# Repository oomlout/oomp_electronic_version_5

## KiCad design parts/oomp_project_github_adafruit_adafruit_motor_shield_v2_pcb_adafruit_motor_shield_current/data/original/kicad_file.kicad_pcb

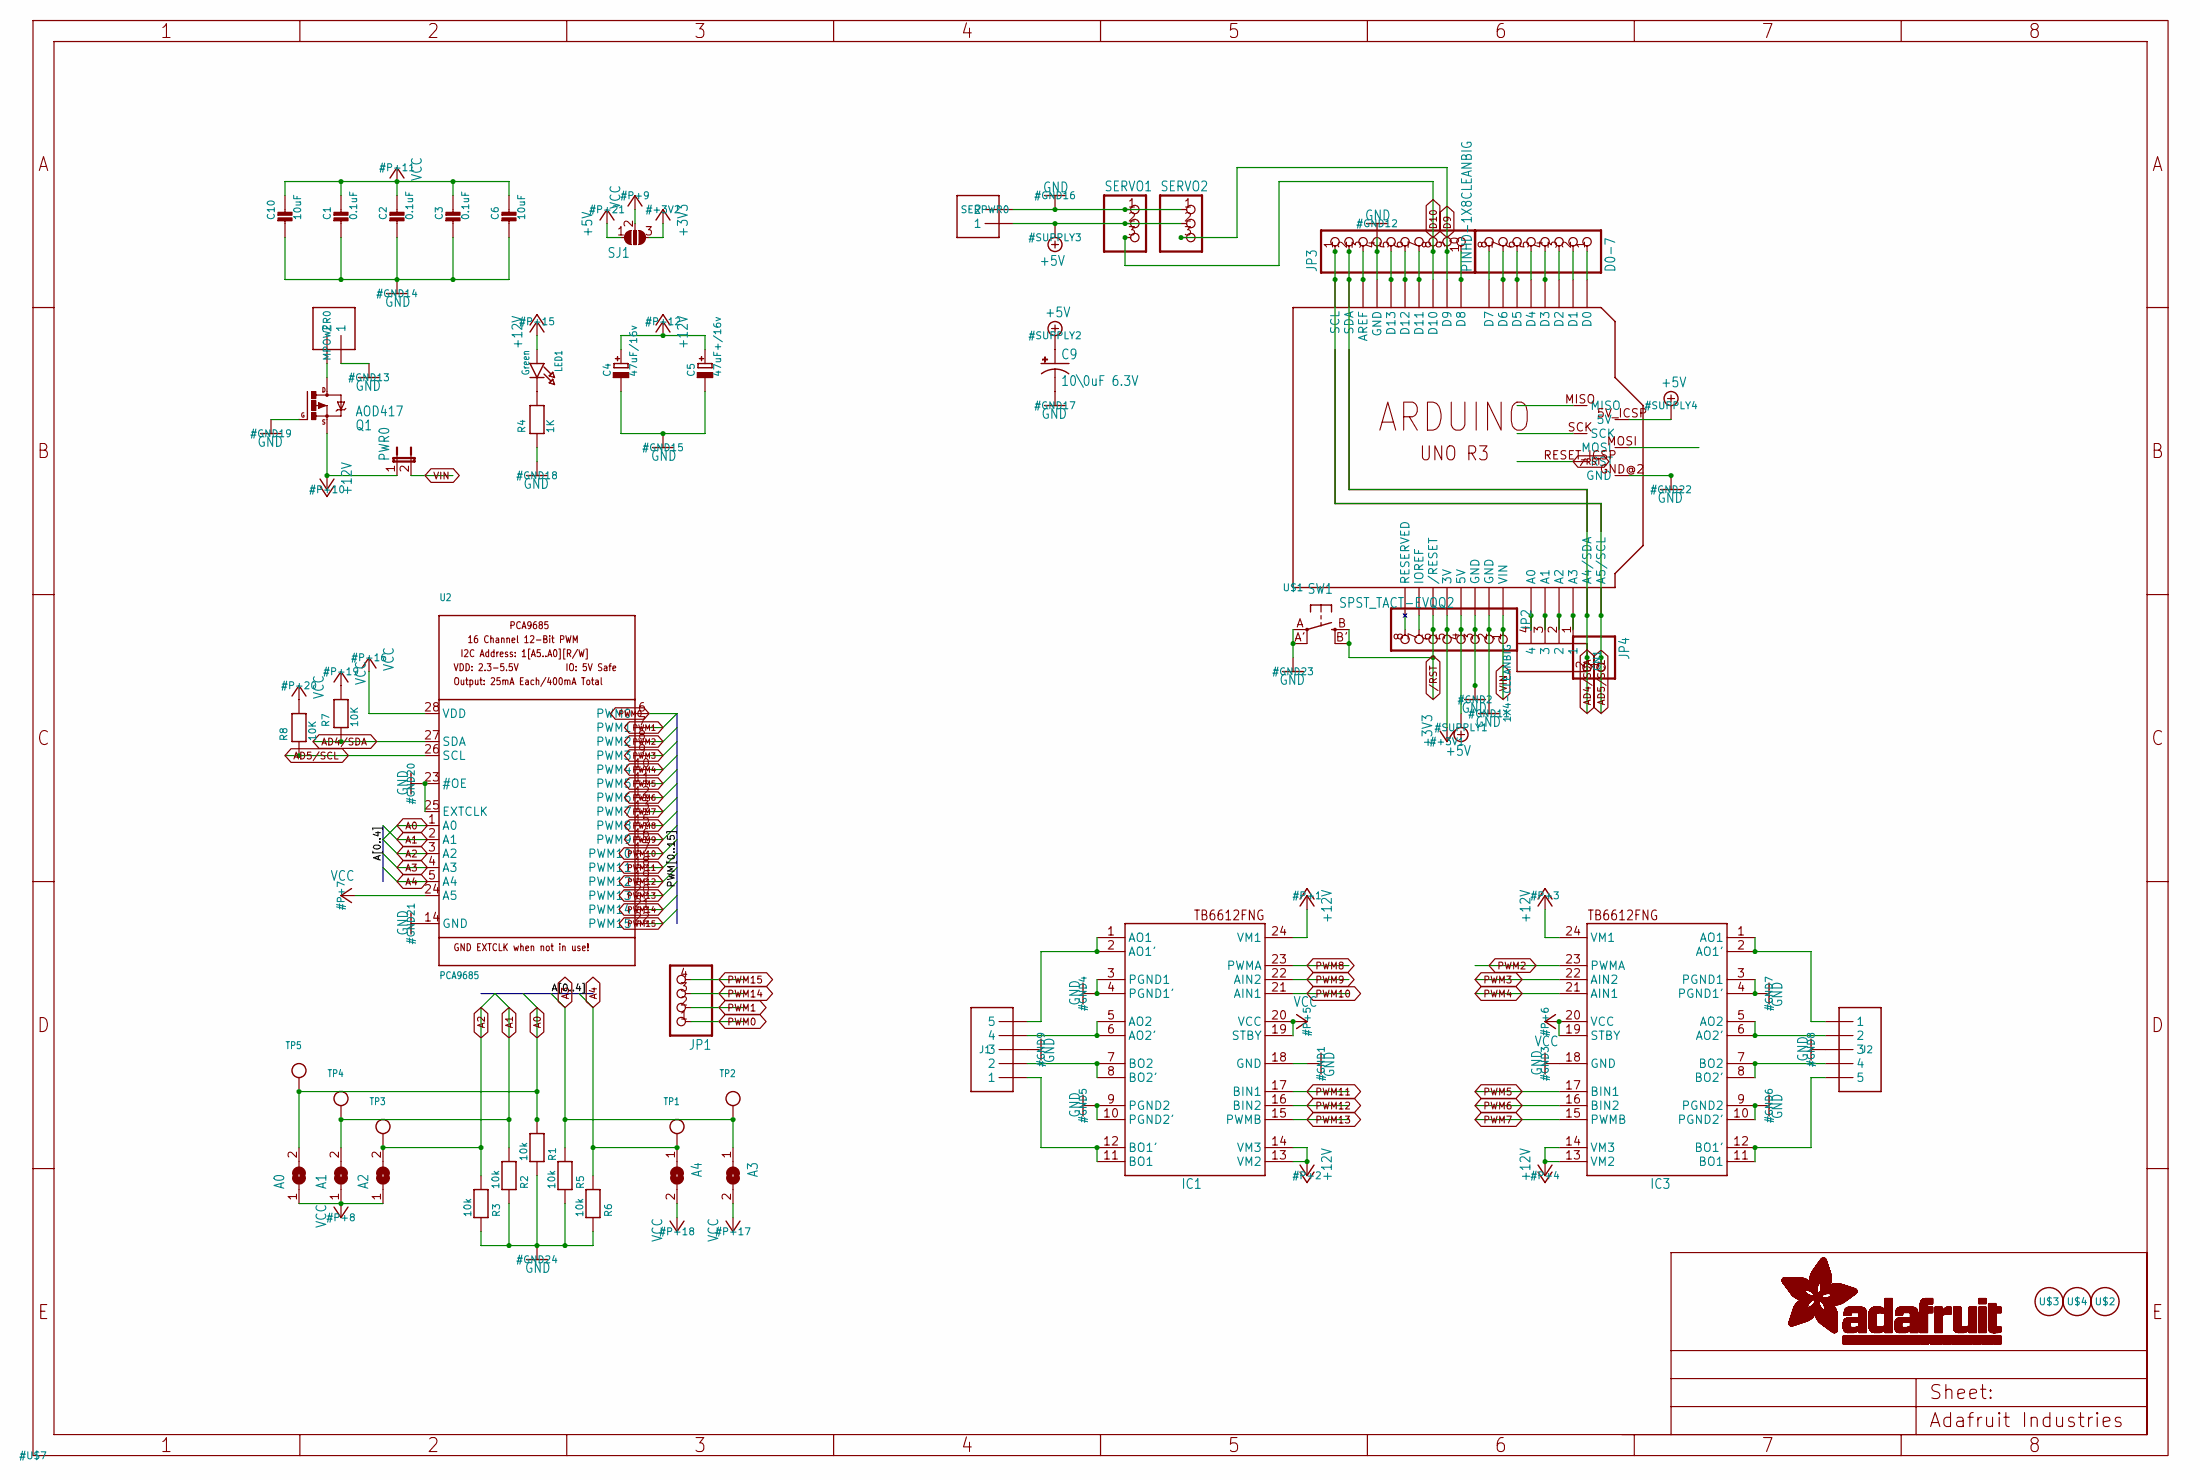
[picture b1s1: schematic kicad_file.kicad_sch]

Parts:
A0, A1, A2, A3, A4: SOLDERJUMPERREFLOW_NOPASTE; SOLDERJUMPER_REFLOW_NOPASTE
C1, C2, C3: 0.1uF; 0805-NO
C4: 47uF/16v; PANASONIC_C
C5: 47uF+/16v; PANASONIC_C
C6, C10: 10uF; 0805-NO
C9: 10\0uF 6.3V; PANASONIC_C
CN1: 1X4-CLEANBIG; 1X04-CLEANBIG
D0-7: PINHD-1X8CLEANBIG; 1X08-CLEANBIG
IC1, IC3: TB6612FNG; SSOP24
J1, J2: 1X5; 1X05-3.5MM
JP1: HEADER-1X476MIL; 1X04_ROUND_76
JP2: PINHD-1X8CLEANBIG; 1X08-CLEANBIG
JP3: HEADER-1X1070MIL; 1X10_ROUND70
JP4: HEADER-1X2ROUND; 1X02_ROUND
LED1: Green; CHIPLED_0805_NOOUTLINE
MPOWER0: 1X2-3.5MM
PWR0: JP1E; JP1
Q1: AOD417; D-PAK_TO252AA
R1, R2, R3, R5, R6: 10k; 0805-NO
R4: 1K; 0805-NO
R7, R8: 10K; 0805-NO
SERPWR0: 1X2-3.5MM
SERVO1, SERVO2: PINHD-1X3; 1X03
SJ1: SOLDERJUMPER_2WAY; SOLDERJUMPER_2WAY_OPEN_NOPASTE
SW1: SPST_TACT-EVQQ2; EVQ-Q2
TP1, TP2, TP3, TP4, TP5: TESTPOINTROUND2MM; TESTPOINT_ROUND_2MM
U2: PCA9685; TSSOP28
U$1: ARDUINO_R3_ICSP; ARDUINOR3_ICSP
U$2, U$3, U$4: FIDUCIAL; FIDUCIAL_1MM

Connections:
+3V3: JP2.5, SJ1.3, U$1.3V
+5V: C9.+, JP2.4, SERPWR0.1, SERVO1.2, SERVO2.2, SJ1.1, U$1.5V, U$1.5V_ICSP (5V)
+12V: C4.+, C5.+, IC1.13 (VM2), IC1.14 (VM3), IC1.24 (VM1), IC3.13 (VM2), IC3.14 (VM3), IC3.24 (VM1), LED1.A, PWR0.1, Q1.3 (S)
/RST: JP2.6, SW1.B (S), SW1.B' (S1), U$1.RESET (/RESET), U$1.RESET_ICSP (RST)
A0: A0.2, R1.2, TP5.P$1, U2.1 (A0)
A1: A1.2, R2.2, TP4.P$1, U2.2 (A1)
A2: A2.2, R3.2, TP3.P$1, U2.3 (A2)
A3: A3.1, R5.2, TP2.P$1, U2.4 (A3)
A4: A4.1, R6.2, TP1.P$1, U2.5 (A4)
AD0: CN1.4, U$1.A0
AD1: CN1.3, U$1.A1
AD2: CN1.2, U$1.A2
AD3: CN1.1, U$1.A3
AD4/SDA: JP3.2, JP4.2, R7.1, U2.27 (SDA), U$1.A4 (A4/SDA), U$1.SDA
AD5/SCL: JP3.1, JP4.1, R8.1, U2.26 (SCL), U$1.A5 (A5/SCL), U$1.SCL
AREF: JP3.3, U$1.AREF
D0: D0-7.1, U$1.D0
D1: D0-7.2, U$1.D1
D2: D0-7.3, U$1.D2
D3: D0-7.4, U$1.D3
D4: D0-7.5, U$1.D4
D5: D0-7.6, U$1.D5
D6: D0-7.7, U$1.D6
D7: D0-7.8, U$1.D7
D8: JP3.10, U$1.D8
D9: JP3.9, SERVO2.3, U$1.D9
D10: JP3.8, SERVO1.3, U$1.D10
D11: JP3.7, U$1.D11
D12: JP3.6, U$1.D12
D13: JP3.5, U$1.D13
GND: C1.2, C2.2, C3.2, C4.-, C5.-, C6.2, C9.-, C10.2, IC1.3 (PGND1), IC1.4 (PGND1'), IC1.9 (PGND2), IC1.10 (PGND2'), IC1.18 (GND), IC3.3 (PGND1), IC3.4 (PGND1'), IC3.9 (PGND2), IC3.10 (PGND2'), IC3.18 (GND), J1.3, J2.3, JP2.2, JP2.3, JP3.4, MPOWER0.1, Q1.1 (G), R1.1, R2.1, R3.1, R4.1, R5.1, R6.1, SERPWR0.2, SERVO1.1, SERVO2.1, SW1.A, SW1.A' (P1), U2.14 (GND), U2.23 (#OE), U2.25 (EXTCLK), U$1.GND, U$1.GND@1 (GND), U$1.GND@2 (GND), U$1.GND@3 (GND)
IOREF: JP2.7, U$1.IOREF
M1A: IC1.1 (AO1), IC1.2 (AO1'), J1.5
M1B: IC1.5 (AO2), IC1.6 (AO2'), J1.4
M2A: IC1.11 (BO1), IC1.12 (BO1'), J1.1
M2B: IC1.7 (BO2), IC1.8 (BO2'), J1.2
M3A: IC3.1 (AO1), IC3.2 (AO1'), J2.1
M3B: IC3.5 (AO2), IC3.6 (AO2'), J2.2
M4A: IC3.11 (BO1), IC3.12 (BO1'), J2.5
M4B: IC3.7 (BO2), IC3.8 (BO2'), J2.4
MISO: U$1.MISO
MOSI: U$1.MOSI
unnamed: JP2.8, U$1.RESERVED
unnamed: LED1.C, R4.2
PWM0: JP1.1, U2.6 (PWM0)
PWM1: JP1.2, U2.7 (PWM1)
PWM2: IC3.23 (PWMA), U2.8 (PWM2)
PWM3: IC3.22 (AIN2), U2.9 (PWM3)
PWM4: IC3.21 (AIN1), U2.10 (PWM4)
PWM5: IC3.17 (BIN1), U2.11 (PWM5)
PWM6: IC3.16 (BIN2), U2.12 (PWM6)
PWM7: IC3.15 (PWMB), U2.13 (PWM7)
PWM8: IC1.23 (PWMA), U2.15 (PWM8)
PWM9: IC1.22 (AIN2), U2.16 (PWM9)
PWM10: IC1.21 (AIN1), U2.17 (PWM10)
PWM11: IC1.17 (BIN1), U2.18 (PWM11)
PWM12: IC1.16 (BIN2), U2.19 (PWM12)
PWM13: IC1.15 (PWMB), U2.20 (PWM13)
PWM14: JP1.3, U2.21 (PWM14)
PWM15: JP1.4, U2.22 (PWM15)
SCK: U$1.SCK
VCC: A0.1, A1.1, A2.1, A3.2, A4.2, C1.1, C2.1, C3.1, C6.1, C10.1, IC1.19 (STBY), IC1.20 (VCC), IC3.19 (STBY), IC3.20 (VCC), R7.2, R8.2, SJ1.2, U2.24 (A5), U2.28 (VDD)
VIN: JP2.1, PWR0.2, U$1.VIN
VMOTOR: MPOWER0.2, Q1.4 (D)

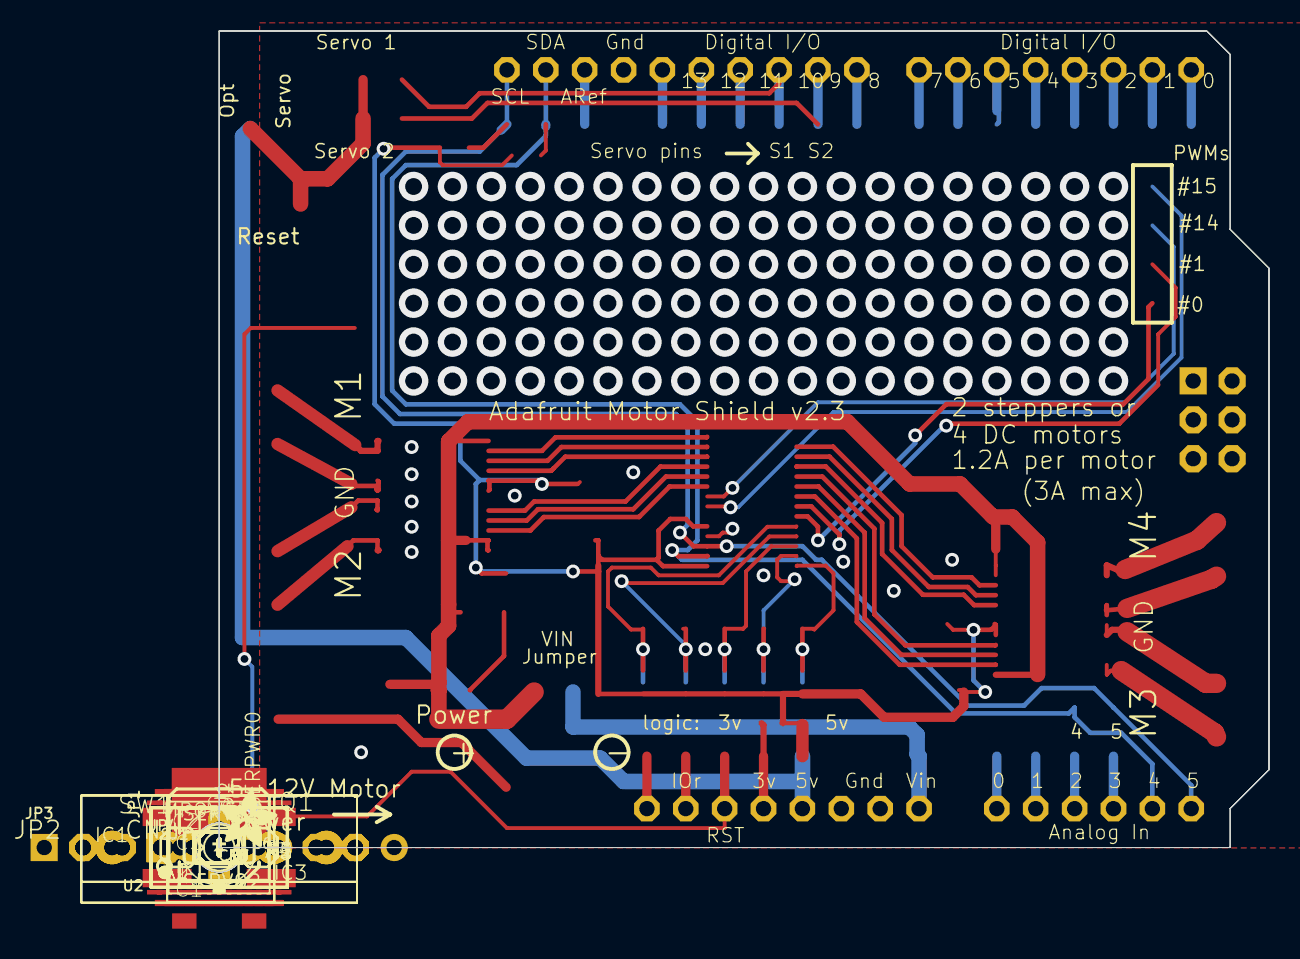
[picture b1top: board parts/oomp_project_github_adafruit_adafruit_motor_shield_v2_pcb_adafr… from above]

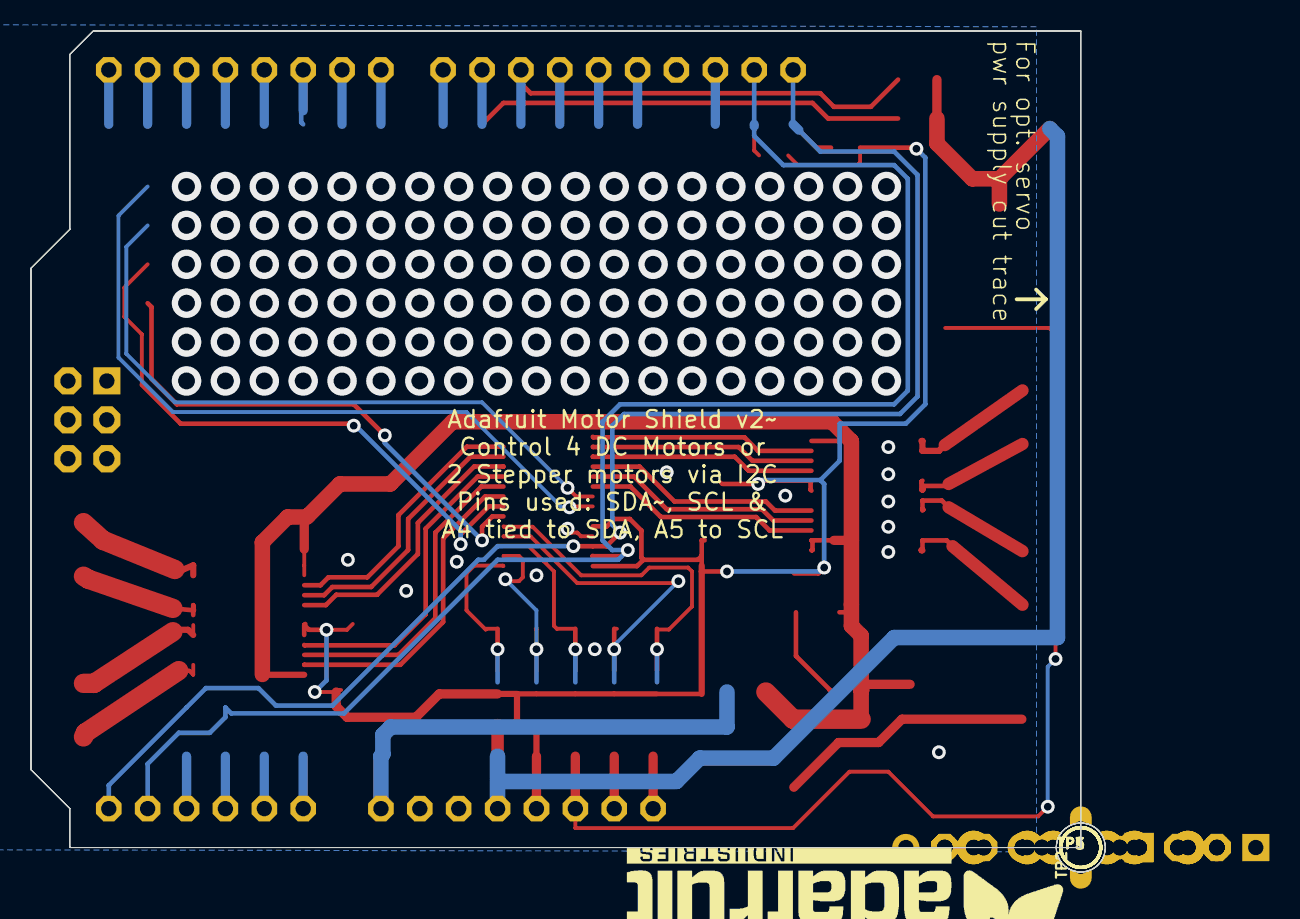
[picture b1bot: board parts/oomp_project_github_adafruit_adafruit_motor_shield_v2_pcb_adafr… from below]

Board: 16 copper layers, 68.6 x 53.3 mm, 55 parts (6 on the bottom side), 61 nets.

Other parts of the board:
U$5: ADAFRUIT_TEXT_30MM
U$6: ADAFRUIT_3.5MM
UNK_HOLE_0: dummyfp0
UNK_HOLE_1: dummyfp1
UNK_HOLE_2: dummyfp2

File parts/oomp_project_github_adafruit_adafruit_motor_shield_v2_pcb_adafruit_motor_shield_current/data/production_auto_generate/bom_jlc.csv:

Comment,Designator,Footprint,LCSC Part #
,JP4,Adafruit Motor Shield v2.3-import-fps:1X02_ROUND,C492401
,"SERVO1,SERVO2",Adafruit Motor Shield v2.3-import-fps:1X03,C49257
,JP1,Adafruit Motor Shield v2.3-import-fps:1X04_ROUND_76,C42431795
,D0-7,Adafruit Motor Shield v2.3-import-fps:1X08-CLEANBIG,
,JP2,Adafruit Motor Shield v2.3-import-fps:1X08-CLEANBIG,C492421
,JP3,Adafruit Motor Shield v2.3-import-fps:1X10_ROUND70,C57369
,U$6,Adafruit Motor Shield v2.3-import-fps:ADAFRUIT_3.5MM,
,U$5,Adafruit Motor Shield v2.3-import-fps:ADAFRUIT_TEXT_30MM,
,PWR0,Adafruit Motor Shield v2.3-import-fps:JP1,
,"A0,A1,A2,A3,A4",Adafruit Motor Shield v2.3-import-fps:SOLDERJUMPER_REFLOW_NOPASTE,
,"TP1,TP2,TP3,TP4,TP5",Adafruit Motor Shield v2.3-import-fps:TESTPOINT_ROUND_2MM,
0.1uF,"C1,C2,C3",Adafruit Motor Shield v2.3-import-fps:0805-NO,
10\0uF 6.3V,C9,Adafruit Motor Shield v2.3-import-fps:PANASONIC_C,
10k,"R1,R2,R3,R5,R6",Adafruit Motor Shield v2.3-import-fps:0805-NO,C17414
10K,"R7,R8",Adafruit Motor Shield v2.3-import-fps:0805-NO,C17414
10uF,"C6,C10",Adafruit Motor Shield v2.3-import-fps:0805-NO,
1K,R4,Adafruit Motor Shield v2.3-import-fps:0805-NO,C17513
1X2-3.5MM,"MPOWER0,SERPWR0",Adafruit Motor Shield v2.3-import-fps:1X2-3.5MM,C492401
1X4-CLEANBIG,CN1,Adafruit Motor Shield v2.3-import-fps:1X04-CLEANBIG,
1X5,"J1,J2",Adafruit Motor Shield v2.3-import-fps:1X05-3.5MM,C42431835
47uF+/16v,C5,Adafruit Motor Shield v2.3-import-fps:PANASONIC_C,
47uF/16v,C4,Adafruit Motor Shield v2.3-import-fps:PANASONIC_C,
AOD417,Q1,Adafruit Motor Shield v2.3-import-fps:D-PAK_TO252AA,
ARDUINO_R3_ICSP,U$1,Adafruit Motor Shield v2.3-import-fps:ARDUINOR3_ICSP,
FIDUCIAL,"U$2,U$3,U$4",Adafruit Motor Shield v2.3-import-fps:FIDUCIAL_1MM,
Green,LED1,Adafruit Motor Shield v2.3-import-fps:CHIPLED_0805_NOOUTLINE,
PCA9685,U2,Adafruit Motor Shield v2.3-import-fps:TSSOP28,
SPST_TACT-EVQQ2,SW1,Adafruit Motor Shield v2.3-import-fps:EVQ-Q2,
TB6612FNG,"IC1,IC3",Adafruit Motor Shield v2.3-import-fps:SSOP24,

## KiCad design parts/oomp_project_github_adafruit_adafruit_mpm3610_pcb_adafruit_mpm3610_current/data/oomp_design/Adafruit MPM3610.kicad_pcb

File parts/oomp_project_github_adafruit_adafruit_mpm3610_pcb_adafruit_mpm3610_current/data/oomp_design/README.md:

# OOMP KiCad design copy

Open `Adafruit MPM3610.kicad_pro` (or the `.kicad_pcb` / `.kicad_sch`) in KiCad. Local OOMP libraries are under `libraries/`. Original inputs are preserved in [../original/](../original/).

Only verified unchanged installed KiCad defaults were renamed. Modified, custom, unmatched and unavailable items remain unchanged. Soldering variants are never swapped during conversion. Existing pad coordinates, nets and UUIDs are preserved.

See [conversion_report.yaml](conversion_report.yaml) for every conversion and skip. Copy this directory before editing; regeneration refuses to overwrite edited design files.

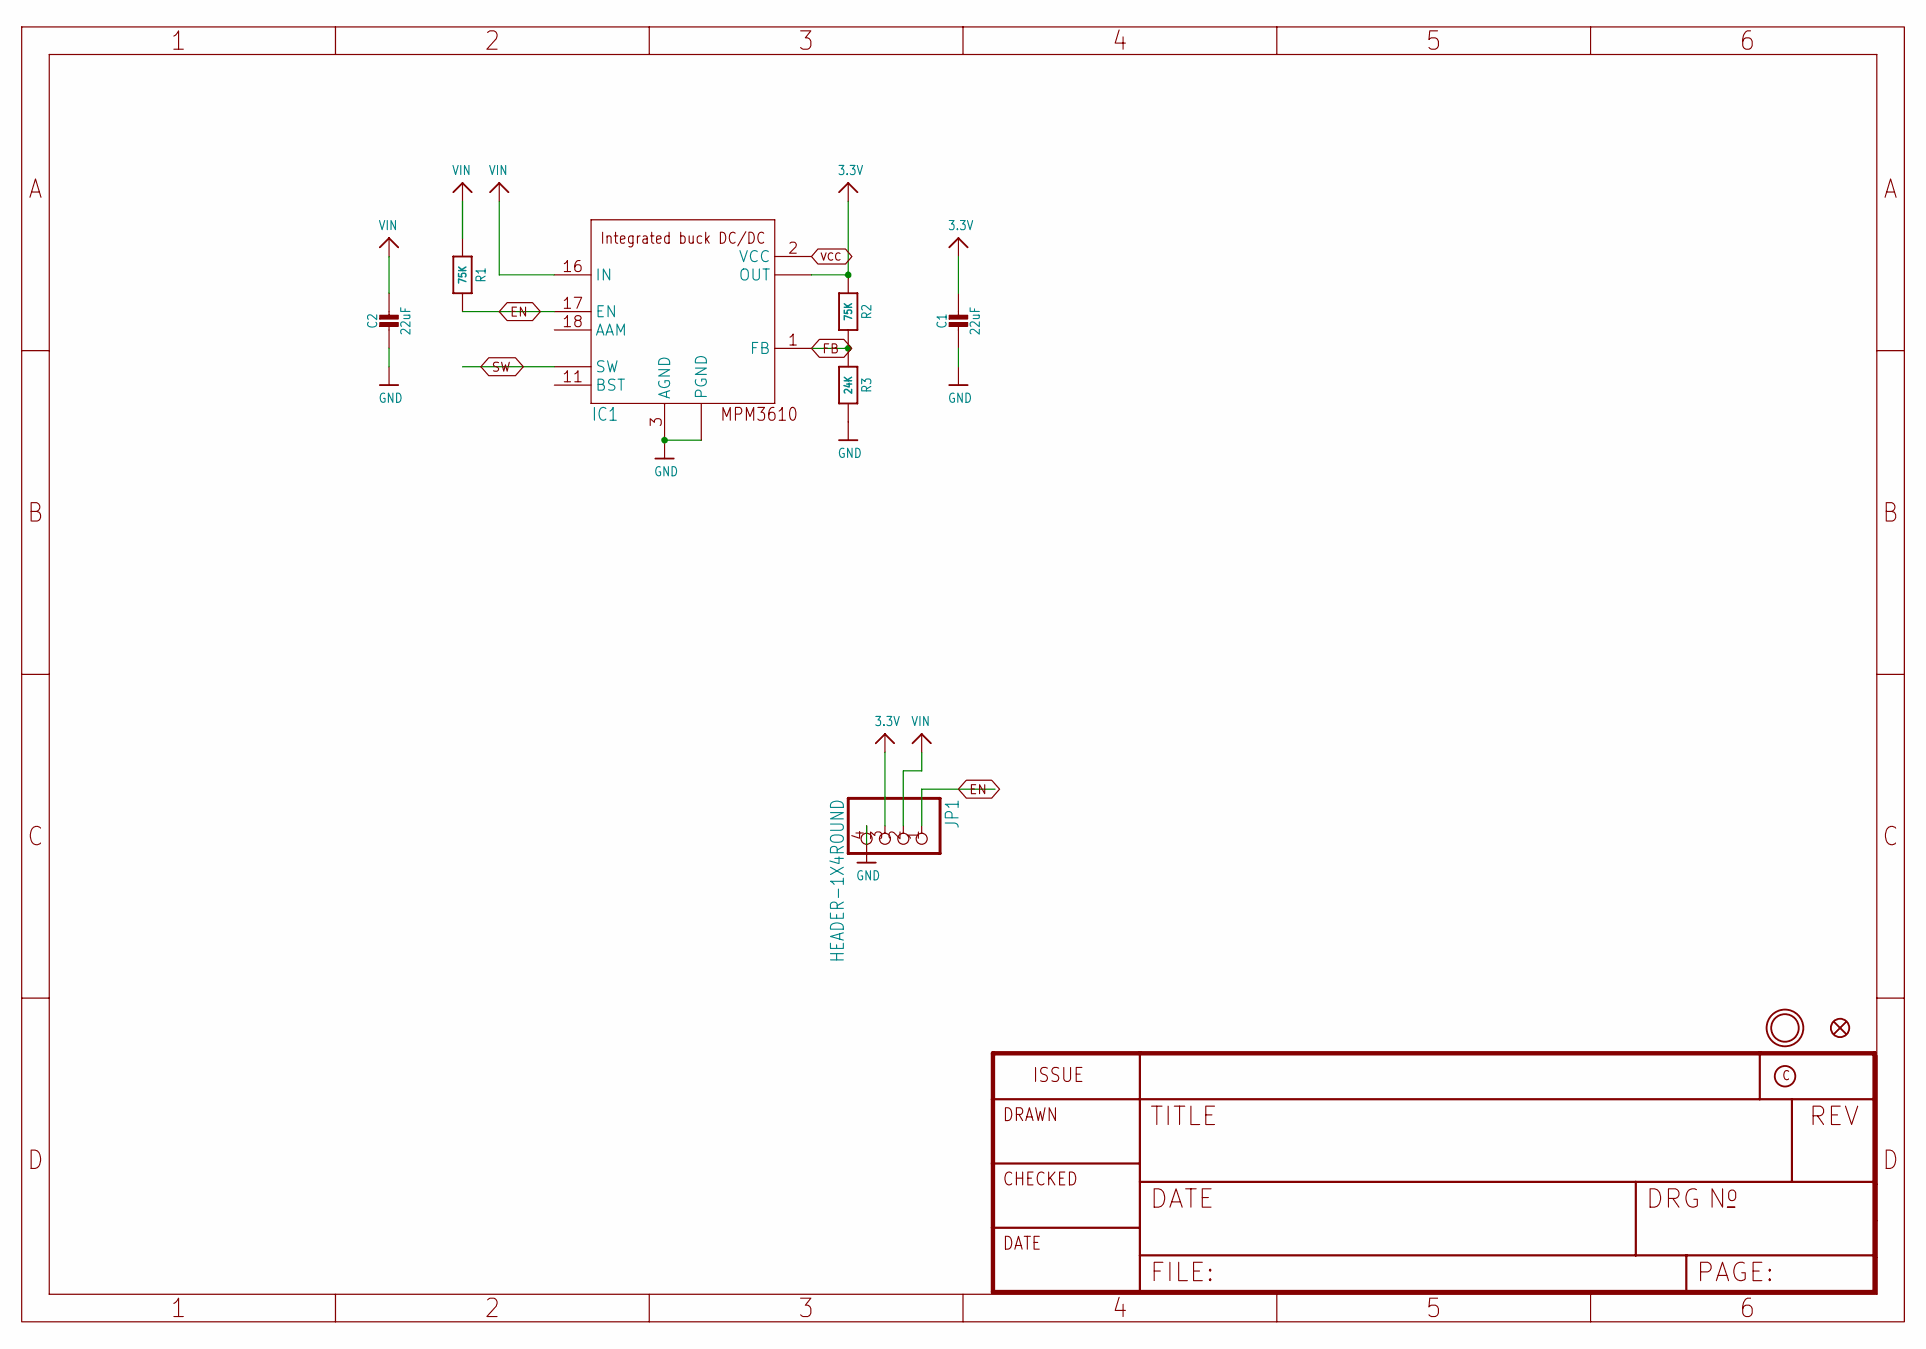
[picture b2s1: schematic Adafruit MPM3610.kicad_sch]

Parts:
C1, C2: 22uF; 0805-NO
FID1: FIDUCIAL_1MM
IC1: MPM3610
JP1: HEADER-1X4ROUND; 1X04_ROUND
R1, R2: 75K; 0603-NO
R3: 24K; 0603-NO
U$9: MOUNTINGHOLE2.5; MOUNTINGHOLE_2.5_PLATED

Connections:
3.3V: C1.1, IC1.7 (OUT), IC1.8 (OUT), IC1.9 (OUT), JP1.3, R2.1
EN: IC1.17 (EN), JP1.1, R1.2
FB: IC1.1 (FB), R2.2, R3.1
GND: C1.2, C2.2, IC1.3 (AGND), IC1.12 (PGND), IC1.13 (PGND), IC1.14 (PGND), JP1.4, R3.2
SW: IC1.4 (SW), IC1.5 (SW), IC1.6 (SW)
VCC: IC1.2 (VCC)
VIN: C2.1, IC1.16 (IN), JP1.2, R1.1

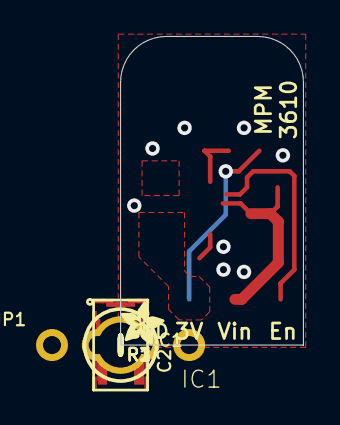
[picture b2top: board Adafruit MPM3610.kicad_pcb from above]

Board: 2 copper layers, 10.2 x 17.1 mm, 11 parts (1 on the bottom side), 6 nets.

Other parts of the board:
U$10: PCBFEAT-REV-040
U$11: ADAFRUIT_2.5MM

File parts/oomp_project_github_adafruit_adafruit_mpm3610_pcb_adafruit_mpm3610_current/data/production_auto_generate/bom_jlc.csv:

Comment,Designator,Footprint,LCSC Part #
,JP1,Adafruit MPM3610-import-fps:1X04_ROUND,C42431795
,U$11,Adafruit MPM3610-import-fps:ADAFRUIT_2.5MM,
,U$10,Adafruit MPM3610-import-fps:PCBFEAT-REV-040,
22uF,"C1,C2",Adafruit MPM3610-import-fps:0805-NO,
24K,R3,Adafruit MPM3610-import-fps:0603-NO,
75K,"R1,R2",Adafruit MPM3610-import-fps:0603-NO,C2907067
MPM3610,IC1,Adafruit MPM3610-import-fps:MPM3610,

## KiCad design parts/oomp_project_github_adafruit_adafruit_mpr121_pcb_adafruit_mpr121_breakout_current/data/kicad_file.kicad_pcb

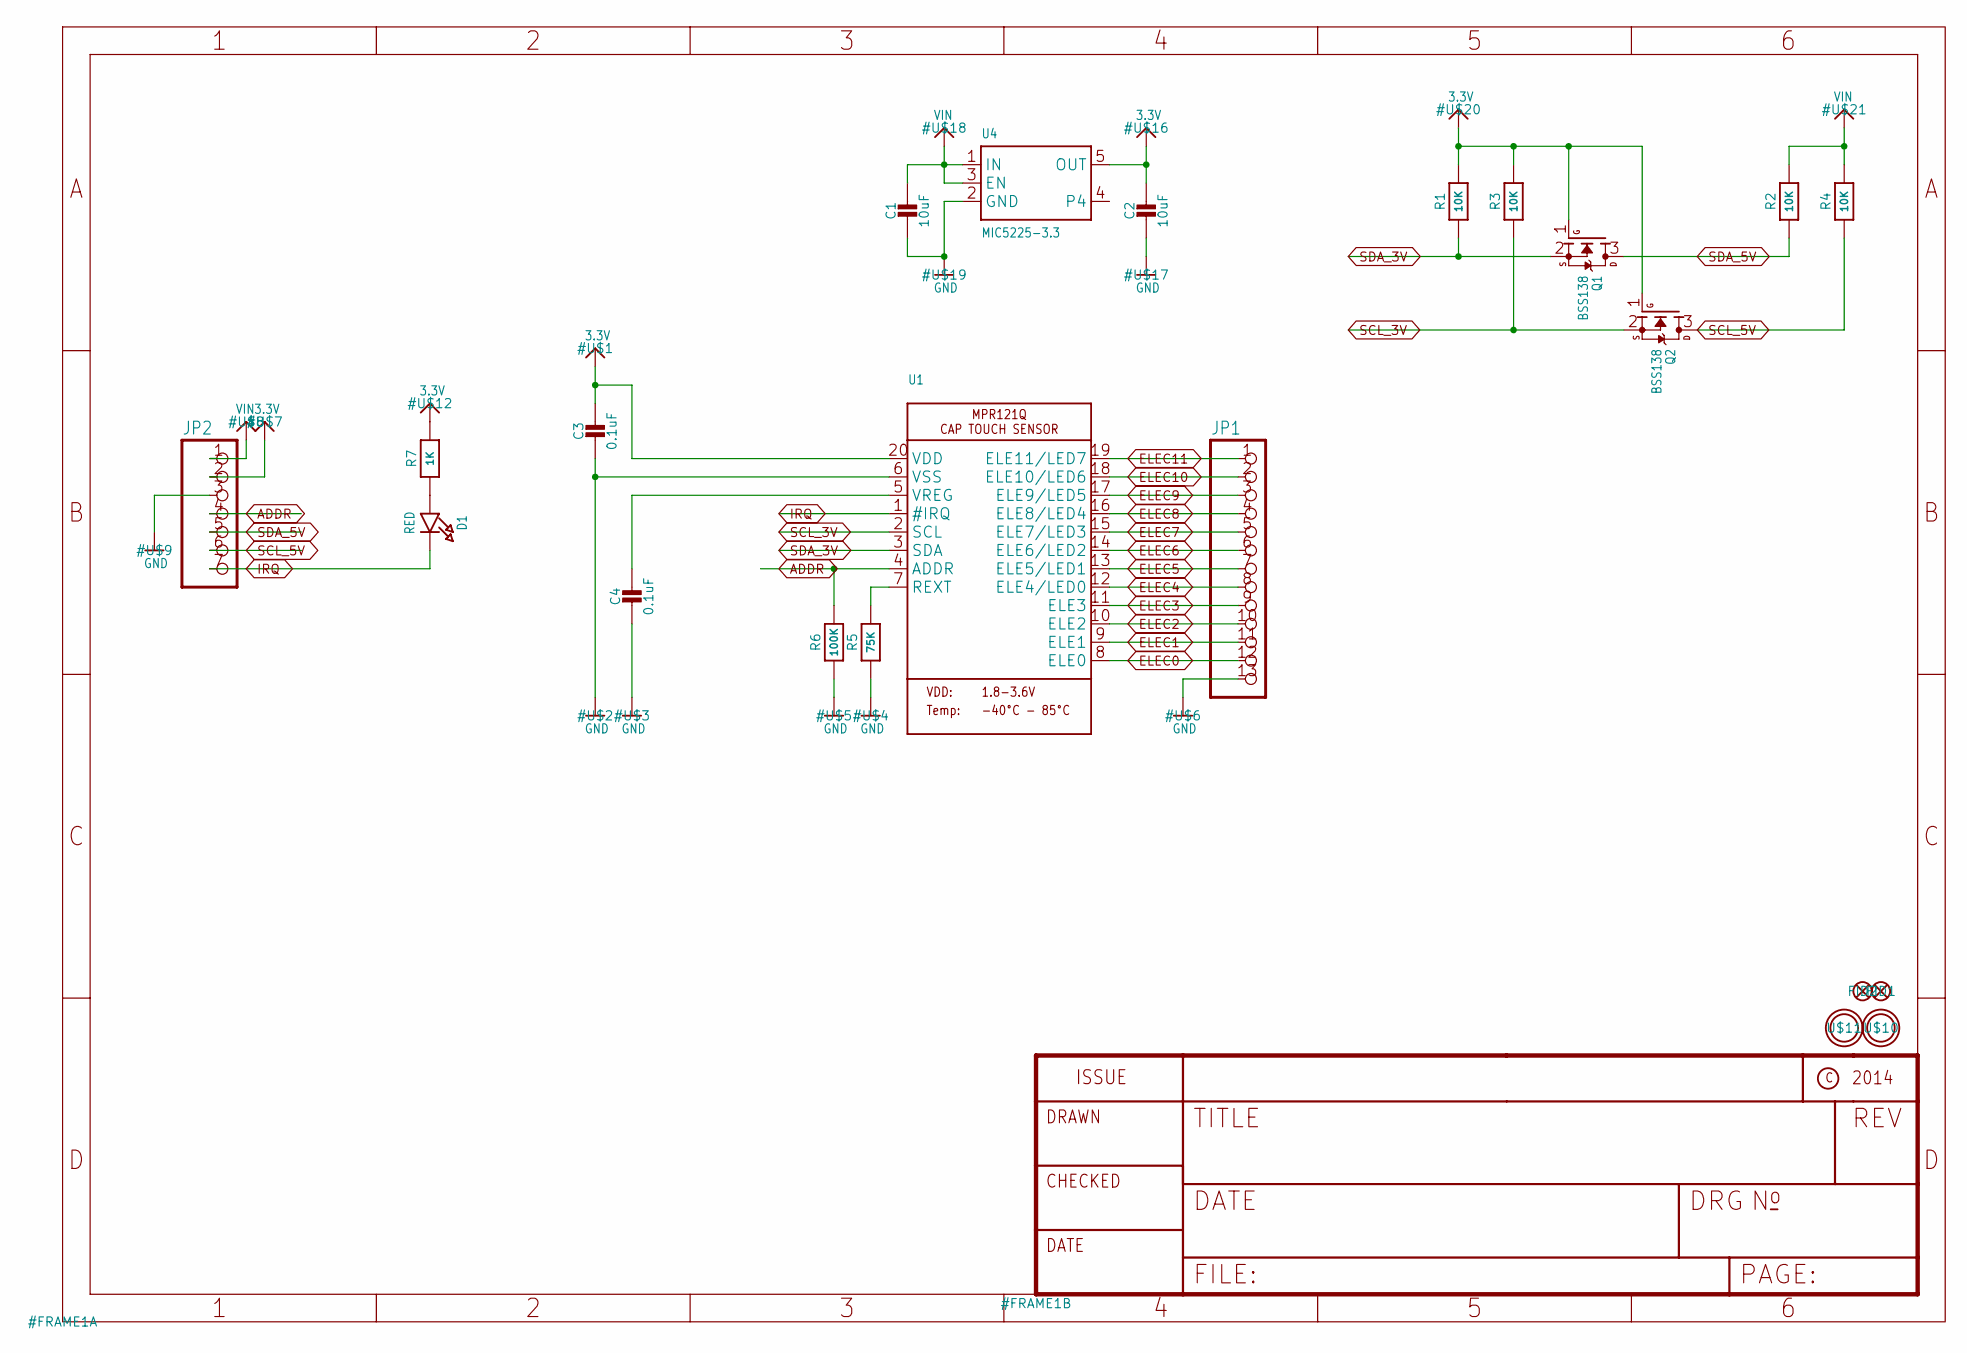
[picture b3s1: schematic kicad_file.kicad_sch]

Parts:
C1, C2: 10uF; 0805-NO
C3: 0.1uF; 0805_10MGAP
C4: 0.1uF; 0805-NO
D1: RED; CHIPLED_0805_NOOUTLINE
FID1, FID2: FIDUCIAL""; FIDUCIAL_1MM
JP1: HEADER-1X13; 1X13_ROUND_70
JP2: HEADER-1X770MIL; 1X07_ROUND_70
Q1, Q2: BSS138; SOT23-WIDE
R1, R2, R3, R4: 10K; 0805-NO
R5: 75K; 0805-NO
R6: 100K; 0805-NO
R7: 1K; 0805-NO
U1: MPR121Q; QFN20_3MM_NOTHERMAL
U4: MIC5225-3.3; SOT23-5
U$10, U$11: MOUNTINGHOLE2.5; MOUNTINGHOLE_2.5_PLATED

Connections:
3.3V: C2.1, C3.1, JP2.2, Q1.1 (G), Q2.1 (G), R1.2, R3.2, R7.2, U1.20 (VDD), U4.5 (OUT)
ADDR: JP2.4, R6.2, U1.4 (ADDR)
ELEC0: JP1.12, U1.8 (ELE0)
ELEC1: JP1.11, U1.9 (ELE1)
ELEC2: JP1.10, U1.10 (ELE2)
ELEC3: JP1.9, U1.11 (ELE3)
ELEC4: JP1.8, U1.12 (ELE4/LED0)
ELEC5: JP1.7, U1.13 (ELE5/LED1)
ELEC6: JP1.6, U1.14 (ELE6/LED2)
ELEC7: JP1.5, U1.15 (ELE7/LED3)
ELEC8: JP1.4, U1.16 (ELE8/LED4)
ELEC9: JP1.3, U1.17 (ELE9/LED5)
ELEC10: JP1.2, U1.18 (ELE10/LED6)
ELEC11: JP1.1, U1.19 (ELE11/LED7)
GND: C1.2, C2.2, C3.2, C4.2, JP1.13, JP2.3, R5.1, R6.1, U1.6 (VSS), U4.2 (GND)
IRQ: D1.C, JP2.7, U1.1 (#IRQ)
unnamed: D1.A, R7.1
unnamed: C4.1, U1.5 (VREG)
unnamed: R5.2, U1.7 (REXT)
SCL_3V: Q2.2 (S), R3.1, U1.2 (SCL)
SCL_5V: JP2.6, Q2.3 (D), R4.1
SDA_3V: Q1.2 (S), R1.1, U1.3 (SDA)
SDA_5V: JP2.5, Q1.3 (D), R2.1
VIN: C1.1, JP2.1, R2.2, R4.2, U4.1 (IN), U4.3 (EN)

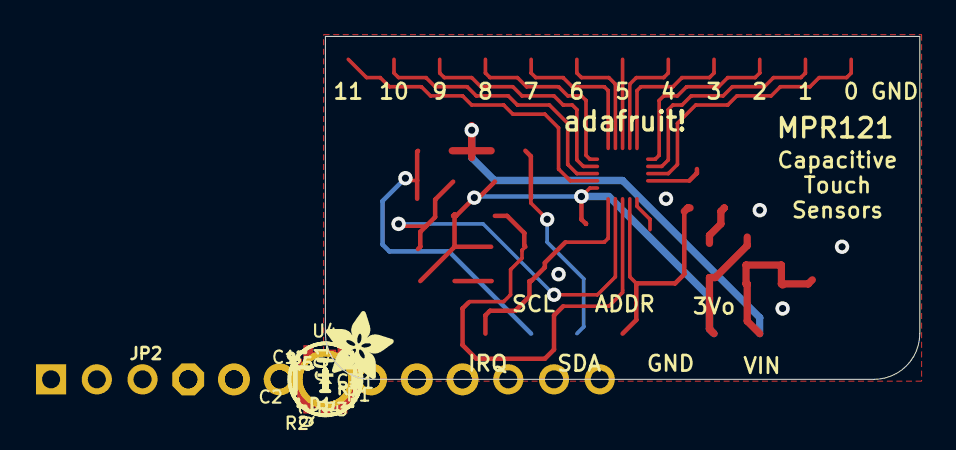
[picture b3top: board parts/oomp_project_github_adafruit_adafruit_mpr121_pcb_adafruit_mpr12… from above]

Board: 2 copper layers, 33.0 x 19.1 mm, 23 parts (0 on the bottom side), 24 nets.

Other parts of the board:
U$14: ADAFRUIT_3.5MM

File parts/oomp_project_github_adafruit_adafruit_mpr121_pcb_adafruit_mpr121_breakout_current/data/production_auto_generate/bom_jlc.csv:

Comment,Designator,Footprint,LCSC Part #
,JP2,Adafruit MPR121 Breakout-import-fps:1X07_ROUND_70,C7501585
,JP1,Adafruit MPR121 Breakout-import-fps:1X13_ROUND_70,C2894936
,U$14,Adafruit MPR121 Breakout-import-fps:ADAFRUIT_3.5MM,
,U1,Adafruit MPR121 Breakout-import-fps:QFN20_3MM_NOTHERMAL,
0.1uF,C4,Adafruit MPR121 Breakout-import-fps:0805-NO,
0.1uF,C3,Adafruit MPR121 Breakout-import-fps:0805_10MGAP,
100K,R6,Adafruit MPR121 Breakout-import-fps:0805-NO,C149504
10K,"R1,R2,R3,R4",Adafruit MPR121 Breakout-import-fps:0805-NO,C17414
10uF,"C1,C2",Adafruit MPR121 Breakout-import-fps:0805-NO,
1K,R7,Adafruit MPR121 Breakout-import-fps:0805-NO,C17513
75K,R5,Adafruit MPR121 Breakout-import-fps:0805-NO,C17819
BSS138,"Q1,Q2",Adafruit MPR121 Breakout-import-fps:SOT23-WIDE,C52895
MIC5225-3.3,U4,Adafruit MPR121 Breakout-import-fps:SOT23-5,
RED,D1,Adafruit MPR121 Breakout-import-fps:CHIPLED_0805_NOOUTLINE,

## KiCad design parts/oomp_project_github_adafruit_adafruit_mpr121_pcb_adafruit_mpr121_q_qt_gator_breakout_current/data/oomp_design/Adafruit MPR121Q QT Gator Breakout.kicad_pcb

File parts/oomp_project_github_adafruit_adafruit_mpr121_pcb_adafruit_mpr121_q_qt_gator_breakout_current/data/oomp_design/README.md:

# OOMP KiCad design copy

Open `Adafruit MPR121Q QT Gator Breakout.kicad_pro` (or the `.kicad_pcb` / `.kicad_sch`) in KiCad. Local OOMP libraries are under `libraries/`. Original inputs are preserved in [../original/](../original/).

Only verified unchanged installed KiCad defaults were renamed. Modified, custom, unmatched and unavailable items remain unchanged. Soldering variants are never swapped during conversion. Existing pad coordinates, nets and UUIDs are preserved.

See [conversion_report.yaml](conversion_report.yaml) for every conversion and skip. Copy this directory before editing; regeneration refuses to overwrite edited design files.

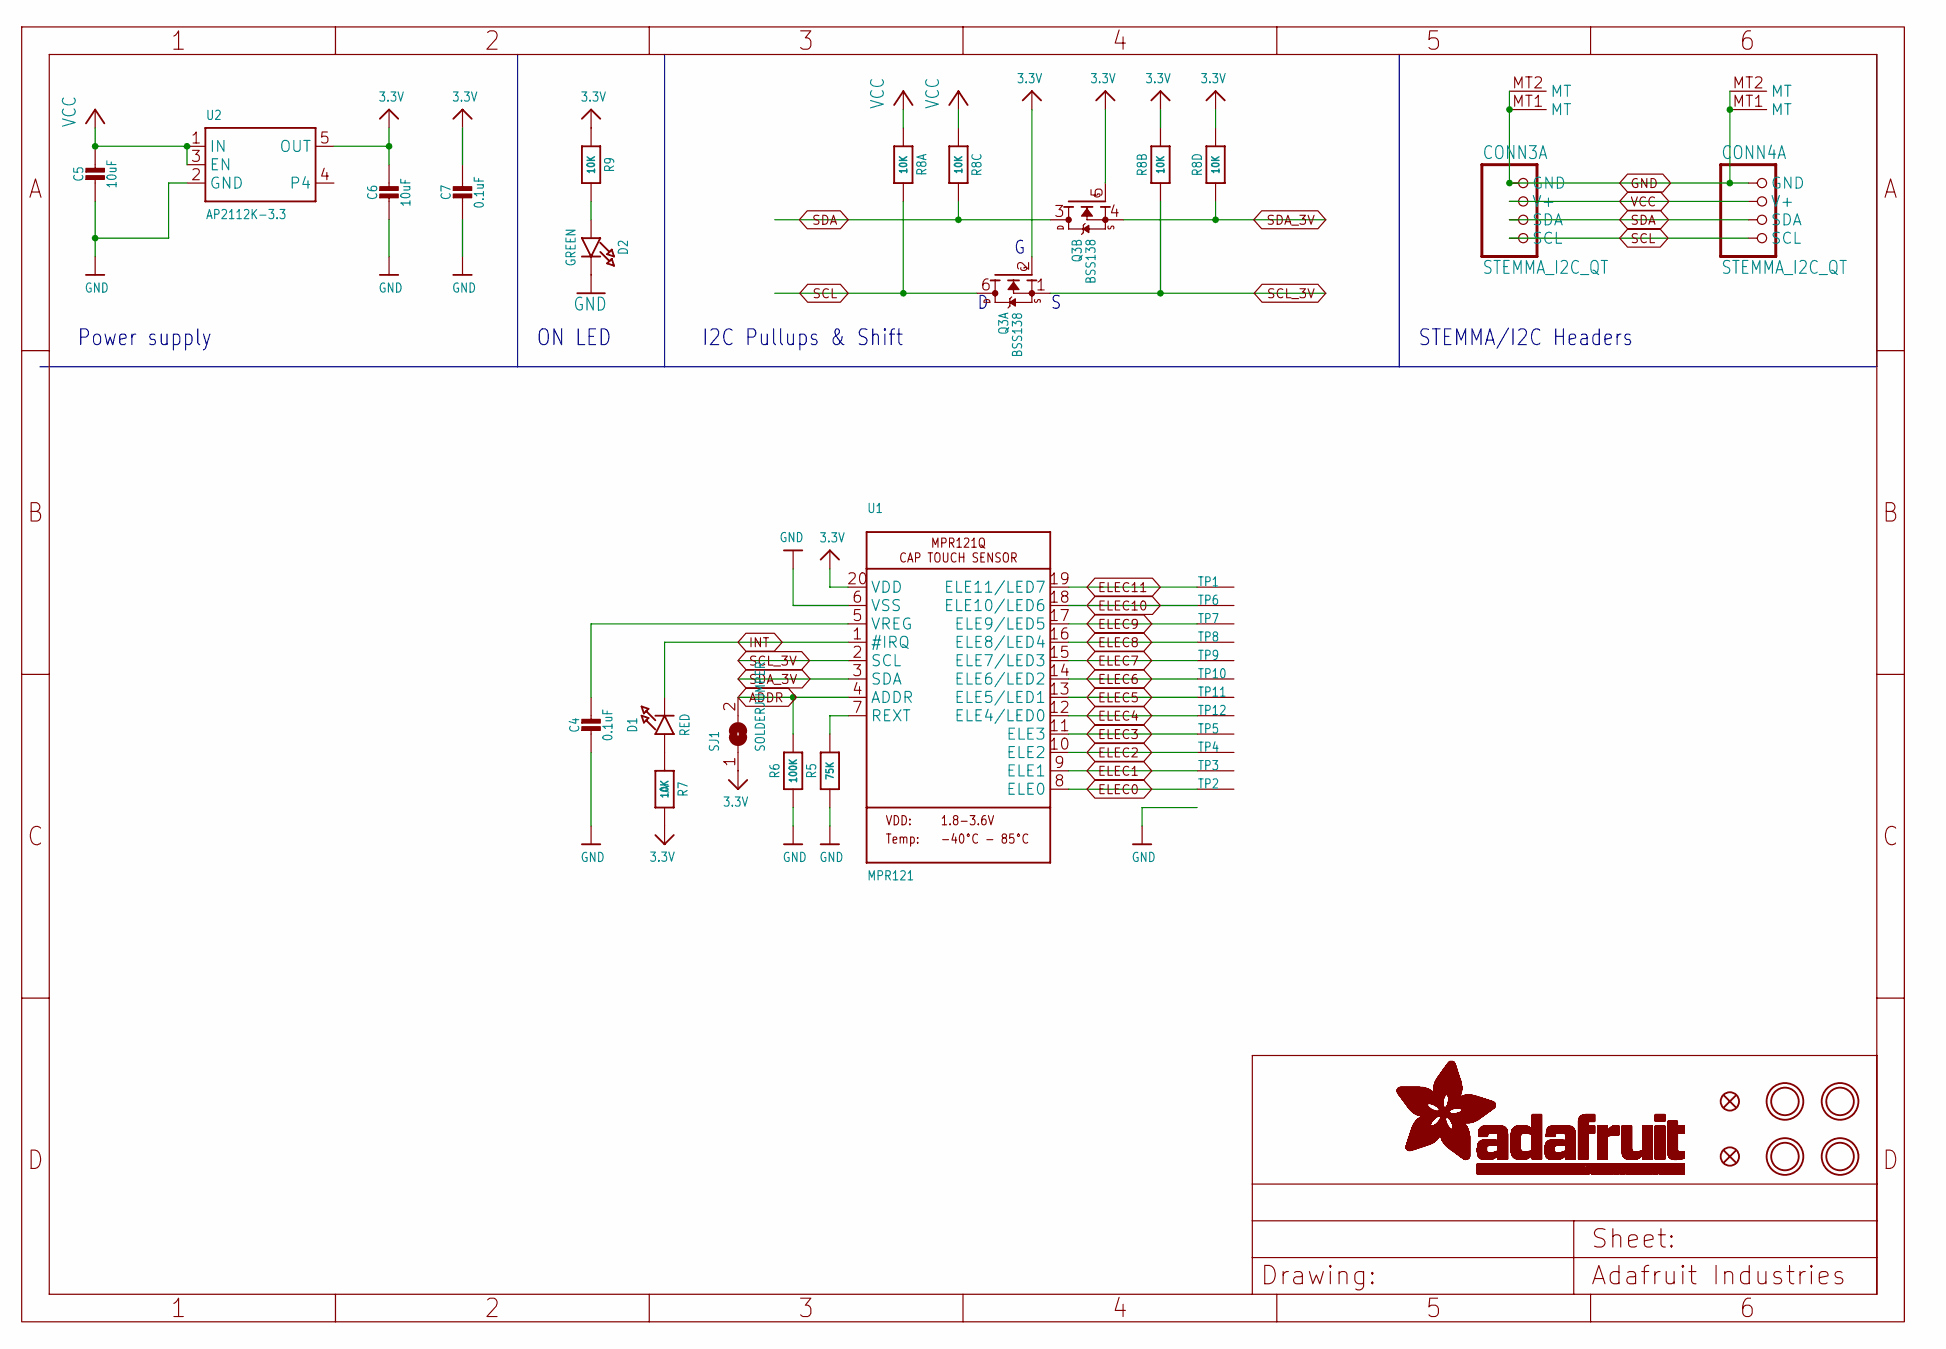
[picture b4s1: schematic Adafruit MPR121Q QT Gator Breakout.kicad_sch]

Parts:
C4, C7: 0.1uF; 0603-NO
C5, C6: 10uF; 0805-NO
CONN3, CONN4: STEMMA_I2C_QT; JST_SH4
D1: RED; CHIPLED_0603_NOOUTLINE
D2: GREEN; CHIPLED_0603_NOOUTLINE
FID3, FID4: FIDUCIAL_1MM
Q3: BSS138; SOT363
R5: 75K; 0603-NO
R6: 100K; 0603-NO
R7, R9: 10K; 0603-NO
R8: 10K; RESPACK_4X0603
SJ1: SOLDERJUMPER; SOLDERJUMPER_ARROW_NOPASTE
TP1, TP2, TP3, TP4, TP5, TP6, TP7, TP8, TP9, TP10, TP11, TP12: SEWTAPPCB_ALLIGATOR; PCB_ALLI
U1: MPR121; QFN20_3MM_NOTHERMAL
U2: AP2112K-3.3; SOT23-5
U$7, U$8, U$34, U$35: MOUNTINGHOLE2.5; MOUNTINGHOLE_2.5_PLATED

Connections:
3.3V: C6.1, C7.1, Q3.2 (G), Q3.5 (G), R7.2, R8.2 (1), R8.4 (1), R9.1, SJ1.1, U1.20 (VDD), U2.5 (OUT)
ADDR: R6.2, SJ1.2, U1.4 (ADDR)
ELEC0: TP2.P$1, U1.8 (ELE0)
ELEC1: TP3.P$1, U1.9 (ELE1)
ELEC2: TP4.P$1, U1.10 (ELE2)
ELEC3: TP5.P$1, U1.11 (ELE3)
ELEC4: TP12.P$1, U1.12 (ELE4/LED0)
ELEC5: TP11.P$1, U1.13 (ELE5/LED1)
ELEC6: TP10.P$1, U1.14 (ELE6/LED2)
ELEC7: TP9.P$1, U1.15 (ELE7/LED3)
ELEC8: TP8.P$1, U1.16 (ELE8/LED4)
ELEC9: TP7.P$1, U1.17 (ELE9/LED5)
ELEC10: TP6.P$1, U1.18 (ELE10/LED6)
ELEC11: TP1.P$1, U1.19 (ELE11/LED7)
GND: C4.2, C5.2, C6.2, C7.2, CONN3.1 (GND), CONN3.MT1 (MT), CONN3.MT2 (MT), CONN4.1 (GND), CONN4.MT1 (MT), CONN4.MT2 (MT), D2.C, R5.1, R6.1, U1.6 (VSS), U2.2 (GND)
INT: D1.C, U1.1 (#IRQ)
unnamed: D1.A, R7.1
unnamed: C4.1, U1.5 (VREG)
unnamed: R5.2, U1.7 (REXT)
unnamed: D2.A, R9.2
SCL: CONN3.4 (SCL), CONN4.4 (SCL), Q3.6 (D), R8.8 (2)
SCL_3V: Q3.1 (S), R8.7 (2), U1.2 (SCL)
SDA: CONN3.3 (SDA), CONN4.3 (SDA), Q3.3 (D), R8.6 (2)
SDA_3V: Q3.4 (S), R8.5 (2), U1.3 (SDA)
VCC: C5.1, CONN3.2 (V+), CONN4.2 (V+), R8.1, R8.3 (1), U2.1 (IN), U2.3 (EN)

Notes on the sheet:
ON LED
I2C Pullups & Shift
STEMMA/I2C Headers
Power supply
